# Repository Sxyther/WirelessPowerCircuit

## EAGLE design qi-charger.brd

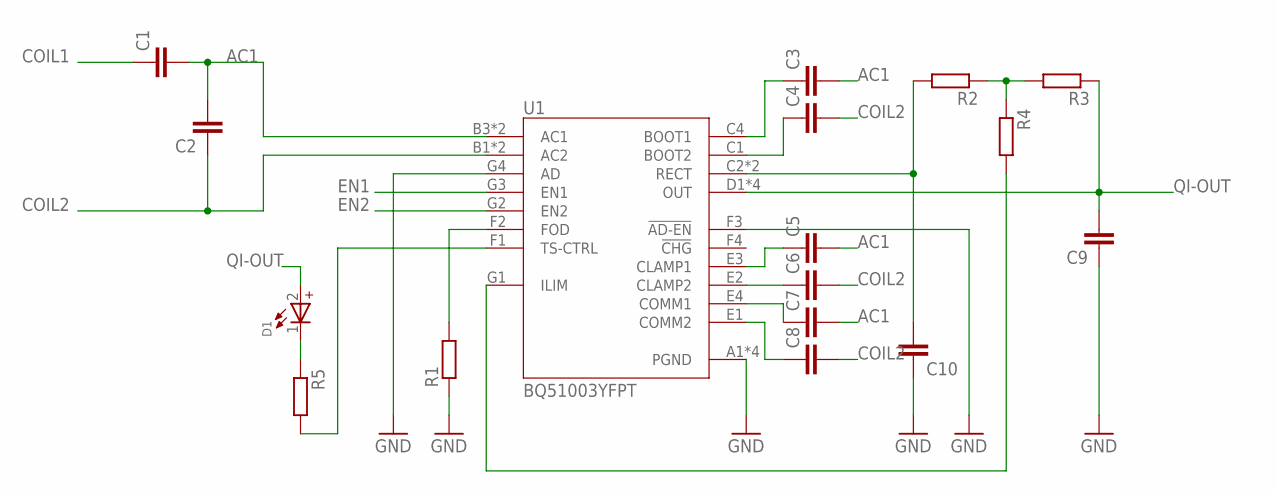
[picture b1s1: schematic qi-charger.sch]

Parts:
C1, C2, C3, C4, C5, C6, C7, C8, C9, C10: C-EUC0805; C0805
D1: WL-SMCW_0603_150060AS75000; WL-SMCW_0603
R1, R2, R3, R4, R5: R-EU_M0805; M0805
U1: BQ51003YFPT; BGA28N40P7X4_300X188X50N

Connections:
AC1: C1.2, C2.2, C3.2, C5.2, C7.2, U1.B3 (AC1), U1.B4 (AC1)
COIL1: C1.1
COIL2: C2.1, C4.2, C6.2, C8.2, U1.B1 (AC2), U1.B2 (AC2)
EN1: U1.G3 (EN1)
EN2: U1.G2 (EN2)
GND: C9.1, C10.1, R1.1, U1.A1 (PGND), U1.A2 (PGND), U1.A3 (PGND), U1.A4 (PGND), U1.F3 (!AD-EN), U1.G4 (AD)
unnamed: R1.2, U1.F2 (FOD)
unnamed: C3.1, U1.C4 (BOOT1)
unnamed: C4.1, U1.C1 (BOOT2)
unnamed: C5.1, U1.E3 (CLAMP1)
unnamed: C6.1, U1.E2 (CLAMP2)
unnamed: C7.1, U1.E4 (COMM1)
unnamed: C8.1, U1.E1 (COMM2)
unnamed: C10.2, R2.2, U1.C2 (RECT), U1.C3 (RECT)
unnamed: R2.1, R3.2, R4.1
unnamed: R4.2, U1.G1 (ILIM)
unnamed: R5.2, U1.F1 (TS-CTRL)
unnamed: D1.1 (-), R5.1
QI-OUT: C9.2, D1.2 (+), R3.1, U1.D1 (OUT), U1.D2 (OUT), U1.D3 (OUT), U1.D4 (OUT)

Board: 2 copper layers, 17 parts (0 on the bottom side), 16 nets, no tracks yet.

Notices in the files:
parts and their libraries:
150120GS75000_Eagle_WL-SMCW_rev20b: Copyright: Würth Elektronik
